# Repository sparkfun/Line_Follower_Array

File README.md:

SparkFun Line Follower Array
========================================

[*SparkFun Line Follower Array (SEN-13582)*](https://www.sparkfun.com/products/13582)

The Sensor Bar takes an 8 bit reading of reflectance for use with following lines or reading dark/light patterns.  The bar can see from about 1/4 to 3/4 inches away.  IR illumination power can be adjusted with the on-board potentiometer.  Illumination can be turned on and off with software to conserve power, or left on all the time for faster readings.

Repository Contents
-------------------

* **/Documentation** - Data sheets, additional product information
* **/Hardware** - Eagle design files (.brd, .sch)
* **/Libraries** - Libraries for use with the RedBot Line Follower Sensor Bar
* **/Production** - Production panel files (.brd)

Documentation
--------------
* **[Library](https://github.com/sparkfun/SparkFun_Line_Follower_Array_Arduino_Library)** - Arduino library for the array.
* **[Hookup Guide](https://learn.sparkfun.com/tutorials/sparkfun-line-follower-array-hookup-guide)** - Basic hookup guide for the array.

Product Versions
----------------
* [*SparkFun Line Follower Array (SEN-13582)*](https://www.sparkfun.com/products/13582)

Version History
---------------
* [V_0.4.0](https://github.com/sparkfun/Line_Follower_Array/tree/V_0.4.0) - Last proto version 
* [V_1.0.0](https://github.com/sparkfun/Line_Follower_Array/tree/V_1.0.0) - Release version

License Information
-------------------

This product is _**open source**_! 

Please review the LICENSE.md file for license information. 

If you have any questions or concerns on licensing, please contact techsupport@sparkfun.com.

Distributed as-is; no warranty is given.

- Your friends at SparkFun.

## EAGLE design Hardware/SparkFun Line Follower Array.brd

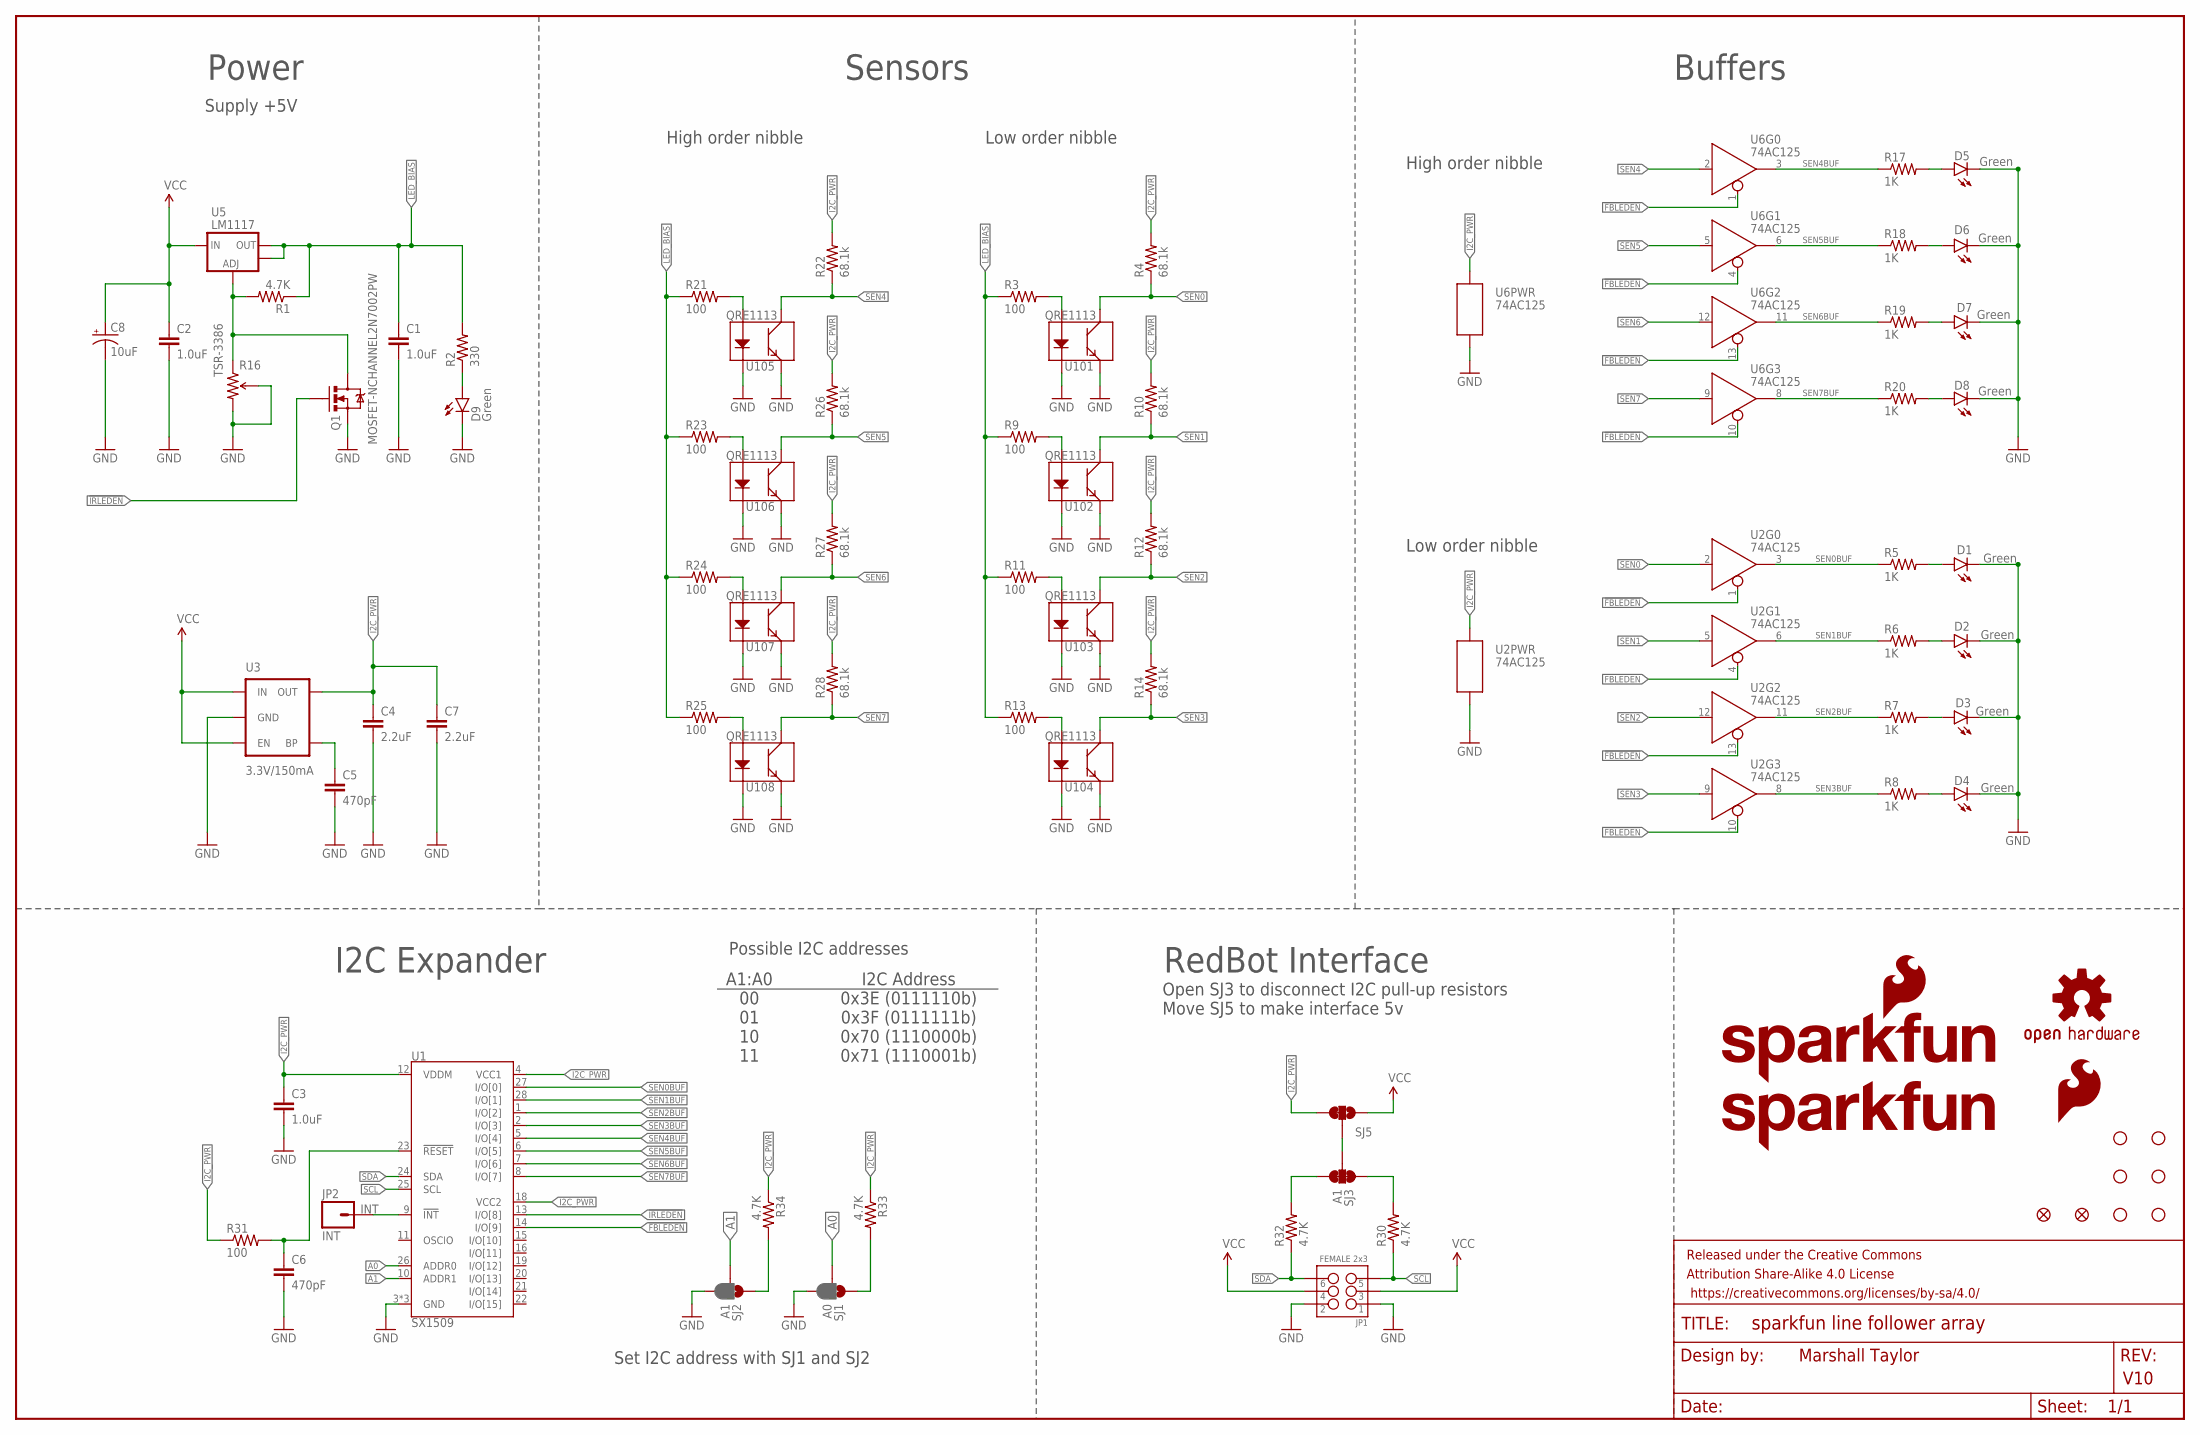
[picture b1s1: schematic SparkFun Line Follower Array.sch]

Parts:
C1, C2, C3: 1.0uF; 0603-CAP
C4, C7: 2.2uF; 0603-CAP
C5, C6: 470pF; 0603-CAP
C8: 10uF; EIA3216
D1, D2, D3, D4, D5, D6, D7, D8, D9: Green; LED-1206-BOTTOM
FID1, FID2: FIDUCIALUFIDUCIAL; MICRO-FIDUCIAL
FRAME2: FRAME-LEDGER; CREATIVE_COMMONS
JP1: FEMALE 2x3; 2X3
JP2: INT; 1X01
LOGO1: SFE_LOGO_NAME_FLAME.2_INCH; SFE_LOGO_NAME_FLAME_.2
LOGO2: SFE_LOGO_NAME.2_INCH; SFE_LOGO_NAME_.2
LOGO5: SFE_LOGO_FLAME.3_INCH; SFE_LOGO_FLAME_.3
LOGO6: OSHW-LOGOS; OSHW-LOGO-S
Q1: MOSFET-NCHANNEL2N7002PW; SOT323
R1, R30, R32, R33, R34: 4.7K; 0603-RES
R2: 330; 0603-RES
R3, R9, R11, R13, R21, R23, R24, R25, R31: 100; 0603-RES
R4, R10, R12, R14, R22, R26, R27, R28: 68.1k; 0603-RES
R5, R6, R7, R8, R17, R18, R19, R20: 1K; 0603-RES
R16: TSR-3386; 3386U
SJ1: A0; PAD-JUMPER-3-2OF3_NC_BY_PASTE_YES_SILK_FULL_BOX
SJ2: A1; PAD-JUMPER-3-2OF3_NC_BY_PASTE_YES_SILK_FULL_BOX
SJ3: A1; PAD-JUMPER-3-3OF3_NC_BY_TRACE_YES_SILK_FULL_BOX
SJ5: JUMPER-PAD-3-2OF3_NC_BY_TRACE_SMALL; PAD-JUMPER-3-2OF3_NC_BY_TRACE_YES_SILK_FULL_BOX
STANDOFF1, STANDOFF2, STANDOFF3, STANDOFF4, STANDOFF5, STANDOFF6: STAND-OFF
U1: SX1509; QFN-28
U2, U6: 74AC125; SO14
U3: 3.3V/150mA; SOT23-5
U5: LM1117; SOT223
U101, U102, U103, U104, U105, U106, U107, U108: QRE1113

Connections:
!FBLEDEN: U1.14 (I/O[9]), U2.1 (!EN), U2.4 (!EN), U2.10 (!EN), U2.13 (!EN), U6.1 (!EN), U6.4 (!EN), U6.10 (!EN), U6.13 (!EN)
!IRLEDEN: Q1.1 (G), U1.13 (I/O[8])
A0: SJ1.2, U1.26 (ADDR0)
A1: SJ2.2, U1.10 (ADDR1)
GND: C1.2, C2.2, C3.2, C4.2, C5.2, C6.2, C7.2, C8.C (-), D1.C, D2.C, D3.C, D4.C, D5.C, D6.C, D7.C, D8.C, D9.C, JP1.1, JP1.2, Q1.2 (S), R16.2 (WIPER), R16.3 (CW), SJ1.3, SJ2.3, U1.3 (GND), U1.17 (GND), U1.29 (GND), U2.7 (P$V-), U3.2 (GND), U6.7 (P$V-), U101.2 (K), U101.4 (E), U102.2 (K), U102.4 (E), U103.2 (K), U103.4 (E), U104.2 (K), U104.4 (E), U105.2 (K), U105.4 (E), U106.2 (K), U106.4 (E), U107.2 (K), U107.4 (E), U108.2 (K), U108.4 (E)
I2C_PWR: C3.1, C4.1, C7.1, R4.2, R10.2, R12.2, R14.2, R22.2, R26.2, R27.2, R28.2, R31.1, R33.1, R34.1, SJ5.3, U1.4 (VCC1), U1.12 (VDDM), U1.18 (VCC2), U2.14 (P$V+), U3.5 (OUT), U6.14 (P$V+)
INT: JP2.1, U1.9 (!INT)
LED_BIAS: C1.1, R1.1, R2.2, R3.1, R9.1, R11.1, R13.1, R21.1, R23.1, R24.1, R25.1, U5.2 (OUT), U5.4 (OUT)
unnamed: Q1.3 (D), R1.2, R16.1 (CCW), U5.1 (ADJ)
unnamed: R3.2, U101.1 (A)
unnamed: R21.2, U105.1 (A)
unnamed: R30.2, SJ3.1
unnamed: D1.A, R5.2
unnamed: C5.1, U3.4 (BP)
unnamed: D2.A, R6.2
unnamed: R32.2, SJ3.3
unnamed: D3.A, R7.2
unnamed: R34.2, SJ2.1
unnamed: D4.A, R8.2
unnamed: R9.2, U102.1 (A)
unnamed: R23.2, U106.1 (A)
unnamed: R11.2, U103.1 (A)
unnamed: R24.2, U107.1 (A)
unnamed: R13.2, U104.1 (A)
unnamed: R25.2, U108.1 (A)
unnamed: D9.A, R2.1
unnamed: SJ3.2, SJ5.2
unnamed: D5.A, R17.2
unnamed: R33.2, SJ1.1
unnamed: D6.A, R18.2
unnamed: D7.A, R19.2
unnamed: D8.A, R20.2
SCL: JP1.5, R30.1, U1.25 (SCL)
SDA: JP1.6, R32.1, U1.24 (SDA)
SEN0: R4.1, U2.2 (D), U101.3 (C)
SEN0BUF: R5.1, U1.27 (I/O[0]), U2.3 (Q)
SEN1: R10.1, U2.5 (D), U102.3 (C)
SEN1BUF: R6.1, U1.28 (I/O[1]), U2.6 (Q)
SEN2: R12.1, U2.12 (D), U103.3 (C)
SEN2BUF: R7.1, U1.1 (I/O[2]), U2.11 (Q)
SEN3: R14.1, U2.9 (D), U104.3 (C)
SEN3BUF: R8.1, U1.2 (I/O[3]), U2.8 (Q)
SEN4: R22.1, U6.2 (D), U105.3 (C)
SEN4BUF: R17.1, U1.5 (I/O[4]), U6.3 (Q)
SEN5: R26.1, U6.5 (D), U106.3 (C)
SEN5BUF: R18.1, U1.6 (I/O[5]), U6.6 (Q)
SEN6: R27.1, U6.12 (D), U107.3 (C)
SEN6BUF: R19.1, U1.7 (I/O[6]), U6.11 (Q)
SEN7: R28.1, U6.9 (D), U108.3 (C)
SEN7BUF: R20.1, U1.8 (I/O[7]), U6.8 (Q)
VCC: C2.1, C8.A (+), JP1.3, JP1.4, SJ5.1, U3.1 (IN), U3.3 (EN), U5.3 (IN)
~RESET: C6.1, R31.2, U1.23 (!RESET)

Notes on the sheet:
Marshall Taylor
V10
Low order nibble
Supply +5V
Sensors
High order nibble
Buffers
Power
RedBot Interface
I2C Expander
Set I2C address with SJ1 and SJ2
Open SJ3 to disconnect I2C pull-up resistors Move SJ5 to make interface 5v
Possible I2C addresses
A1:A0 00 01 10 11
I2C Address 0x3E (0111110b) 0x3F (0111111b) 0x70 (1110000b) 0x71 (1110001b)

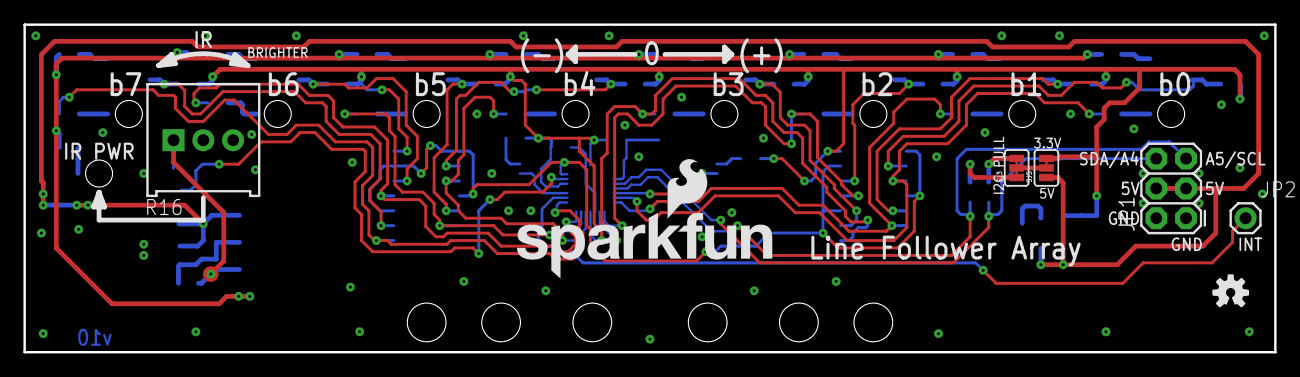
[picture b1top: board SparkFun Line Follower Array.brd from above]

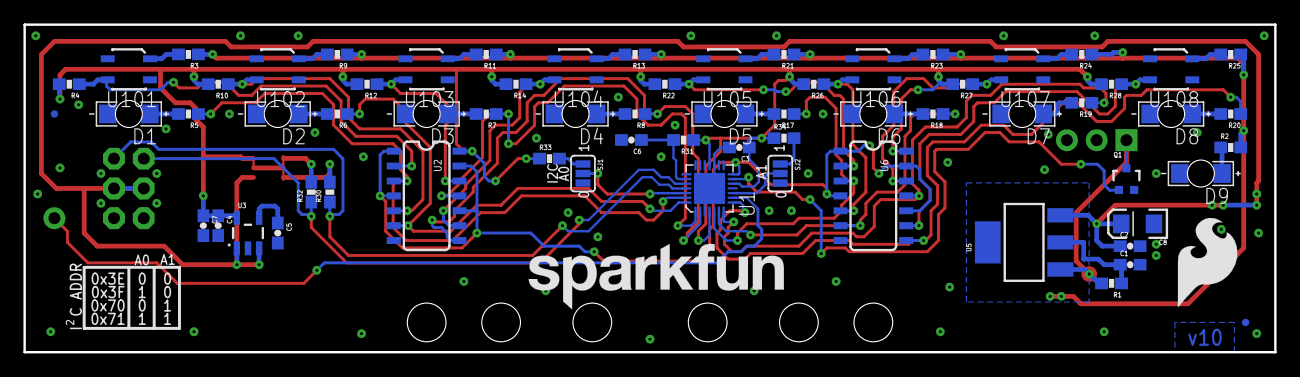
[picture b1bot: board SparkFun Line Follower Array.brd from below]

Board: 2 copper layers, 106.7 x 27.9 mm, 82 parts (68 on the bottom side), 52 nets.

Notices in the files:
parts and their libraries:
SparkFun-Capacitors: Licensing: Creative Commons ShareAlike 4.0 International - https://creativecommons.org/licenses/by-sa/4.0
SparkFun-Connectors: Licensing: CC v3.0 Share-Alike You are welcome to use this library for commercial purposes.
SparkFun-Aesthetics: Released under the Creative Commons
